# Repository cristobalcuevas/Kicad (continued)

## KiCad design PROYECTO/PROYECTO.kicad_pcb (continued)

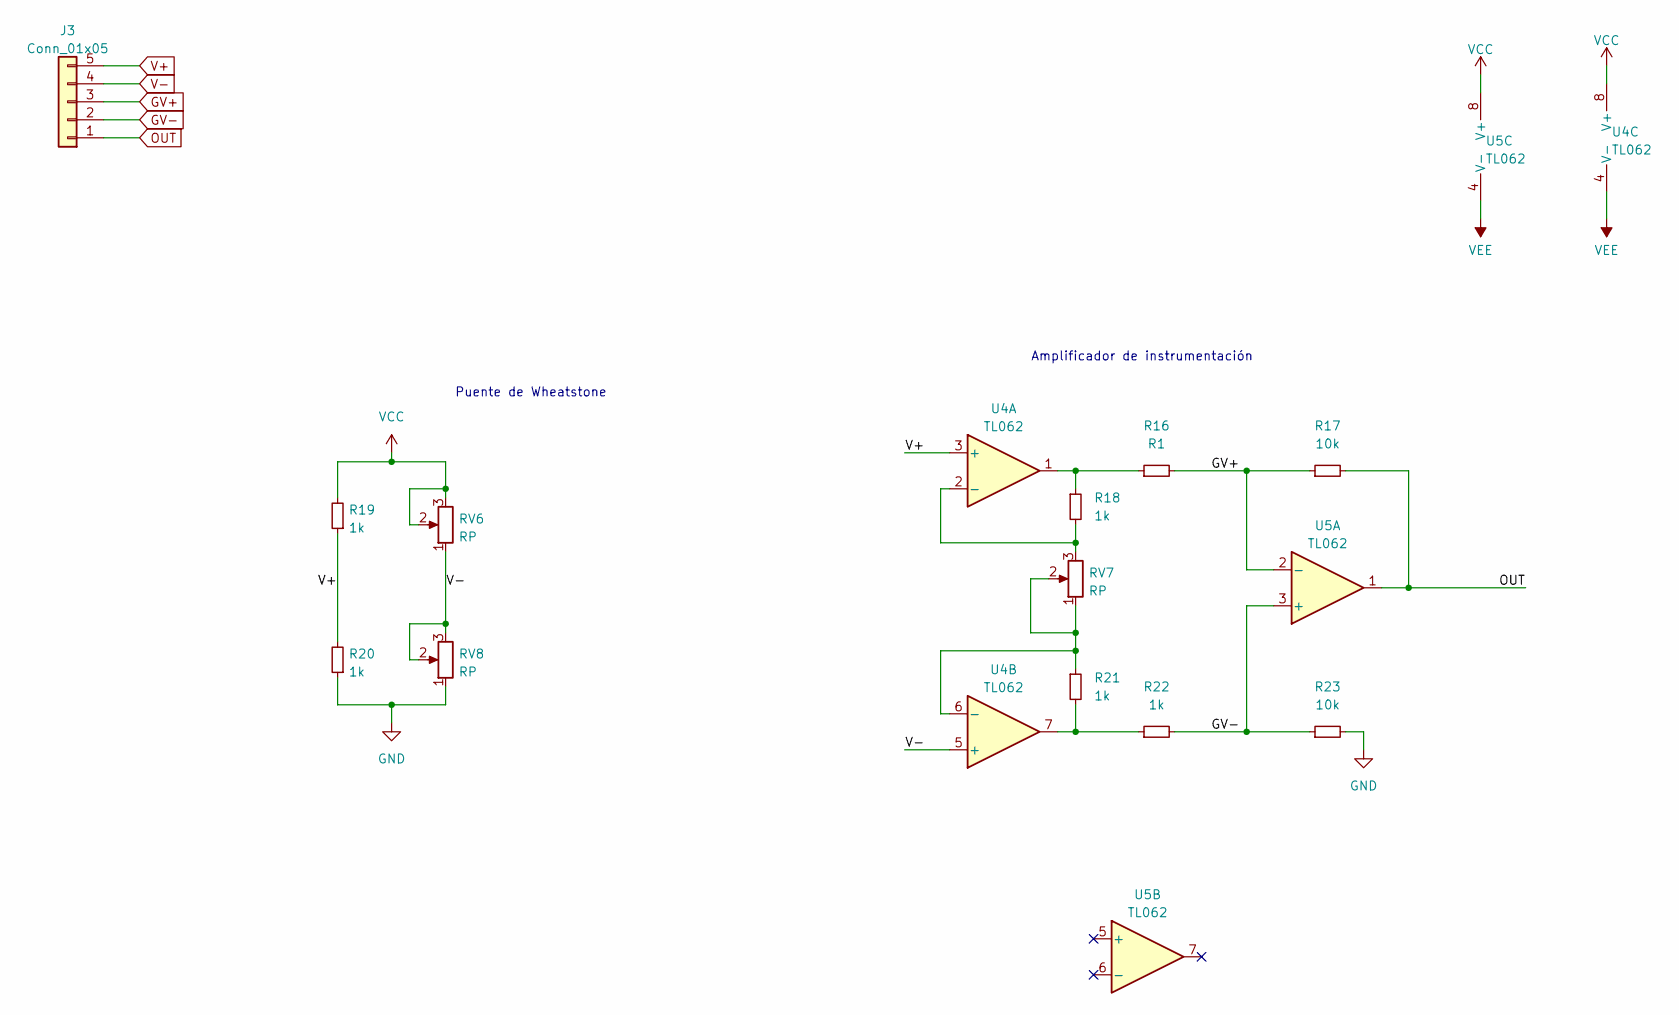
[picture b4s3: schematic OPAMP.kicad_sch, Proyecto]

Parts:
J3: Conn_01x05; PinHeader_1x05_P2.54mm_Vertical
R16: R1; R_Axial_DIN0207_L6.3mm_D2.5mm_P7.62mm_Horizontal
R17, R23: 10k; R_Axial_DIN0207_L6.3mm_D2.5mm_P7.62mm_Horizontal
R18, R19, R20, R21, R22: 1k; R_Axial_DIN0207_L6.3mm_D2.5mm_P7.62mm_Horizontal
RV6, RV7, RV8: RP; PinHeader_1x03_P2.54mm_Vertical
U4, U5: TL062; DIP-8_W7.62mm

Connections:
GND: R20.1, R23.2, RV8.1; also elsewhere on the board
GV+: J3.3, R16.2, R17.1, U5.2 (-)
GV-: J3.2, R22.2, R23.1, U5.3 (+)
unnamed: R16.1, R18.1, U4.1
unnamed: R18.2, RV7.3, U4.2 (-)
unnamed: R21.1, RV7.1, RV7.2, U4.6 (-)
unnamed: R21.2, R22.1, U4.7
OUT: J3.1, R17.2, U5.1
V+: J3.5, R19.1, R20.2, U4.3 (+)
V-: J3.4, RV6.1, RV8.2, RV8.3, U4.5 (+)
VCC: R19.2, RV6.2, RV6.3, U4.8 (V+), U5.8 (V+); also elsewhere on the board
VEE: U4.4 (V-), U5.4 (V-); also elsewhere on the board

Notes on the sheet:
Puente de Wheatstone
Amplificador de instrumentación

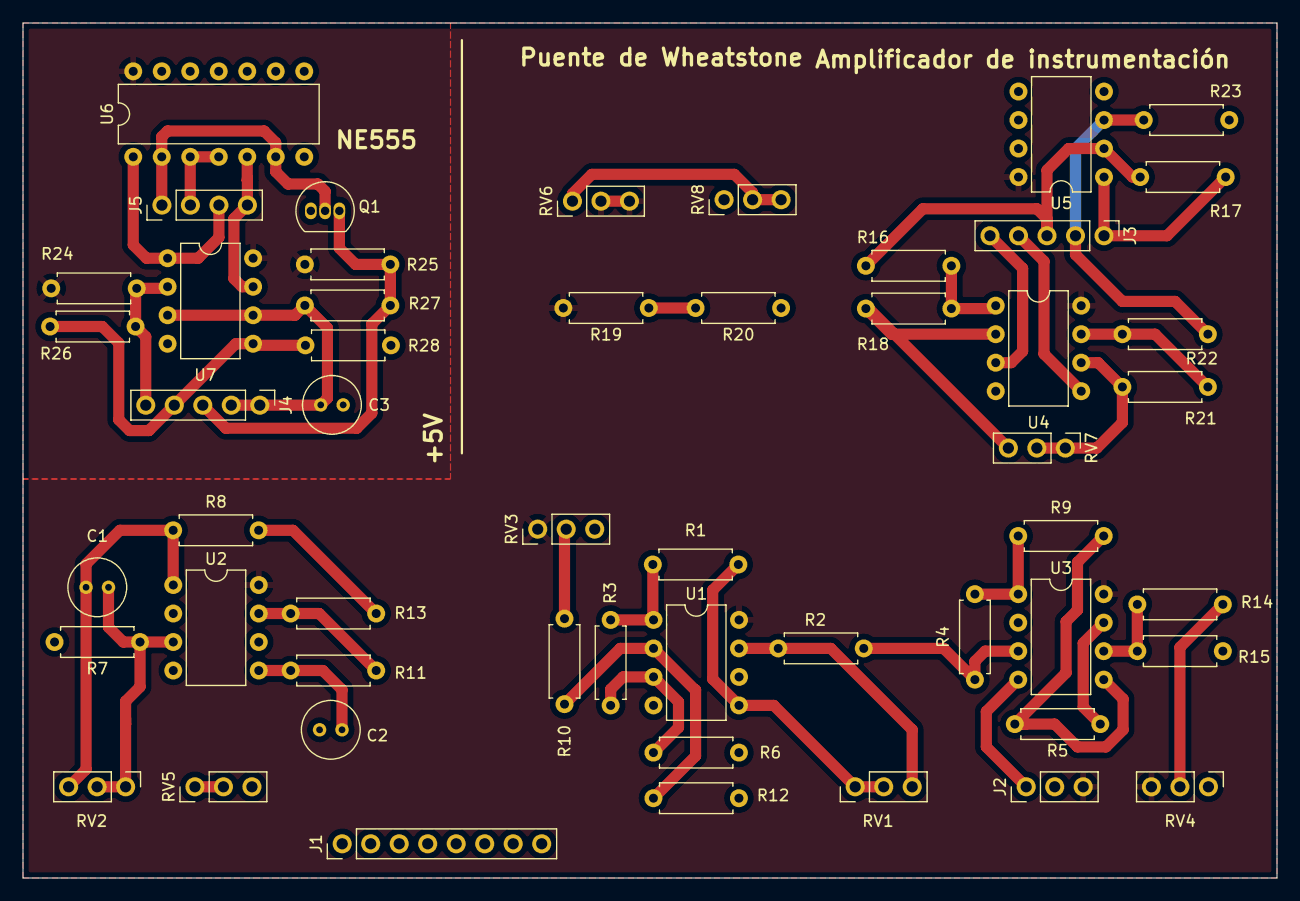
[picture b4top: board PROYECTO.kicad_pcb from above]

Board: 2 copper layers, 111.8 x 76.2 mm, 52 parts (0 on the bottom side), 38 nets.

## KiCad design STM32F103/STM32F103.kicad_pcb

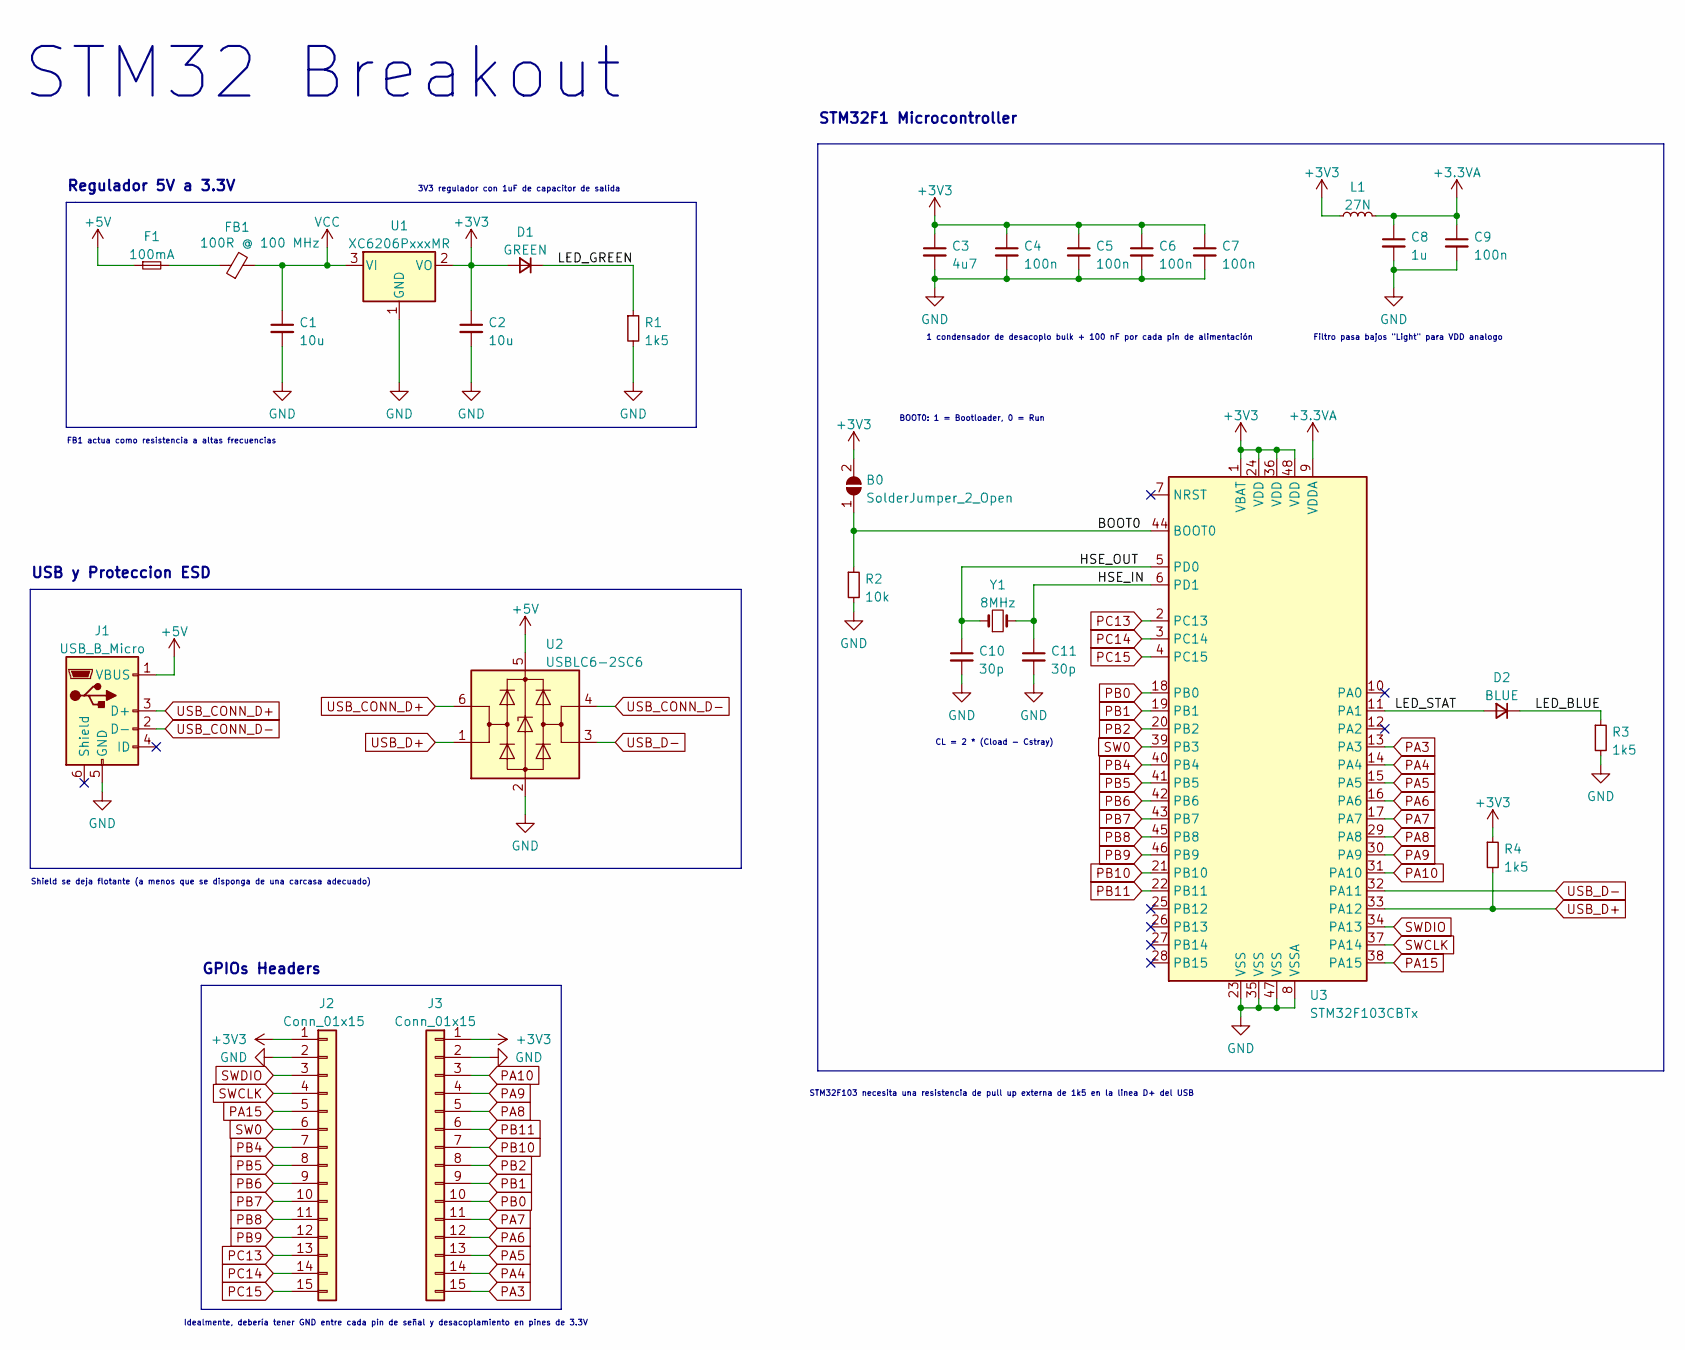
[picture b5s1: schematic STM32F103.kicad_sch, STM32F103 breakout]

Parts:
B0: SolderJumper_2_Open; SolderJumper-2_P1.3mm_Open_Pad1.0x1.5mm
C1, C2: 10u; C_0603_1608Metric
C3: 4u7; C_0603_1608Metric
C4, C5, C6, C7, C9: 100n; C_0402_1005Metric
C8: 1u; C_0402_1005Metric
C10, C11: 30p; C_0402_1005Metric
D1: GREEN; LED_0603_1608Metric
D2: BLUE; LED_0603_1608Metric
F1: 100mA; Fuse_0603_1608Metric
FB1: 100R @ 100 MHz; L_0805_2012Metric
J1: USB_B_Micro; USB_Micro-B_Wuerth_629105150521
J2, J3: Conn_01x15; PinHeader_1x15_P2.54mm_Vertical
L1: 27N; L_0402_1005Metric
R1, R3: 1k5; R_0603_1608Metric
R2: 10k; R_0402_1005Metric
R4: 1k5; R_0402_1005Metric
U1: XC6206PxxxMR; SOT-23
U2: USBLC6-2SC6; SOT-23-6
U3: STM32F103CBTx; LQFP-48_7x7mm_P0.5mm
Y1: 8MHz; Crystal_SMD_5032-2Pin_5.0x3.2mm

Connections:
+3.3VA: C8.1, C9.1, L1.2, U3.9 (VDDA)
+3V3: B0.2 (B), C2.1, C3.1, C4.1, C5.1, C6.1, C7.1, D1.2 (A), J2.1, J3.1, L1.1, R4.1, U1.2 (VO), U3.1 (VBAT), U3.24 (VDD), U3.36 (VDD), U3.48 (VDD)
+5V: F1.1, J1.1 (VBUS), U2.5 (VBUS)
/BOOT0: B0.1 (A), R2.1, U3.44 (BOOT0)
/HSE_IN: C11.1, U3.6 (PD1), Y1.2
/HSE_OUT: C10.1, U3.5 (PD0), Y1.1
/LED_BLUE: D2.1 (K), R3.1
/LED_GREEN: D1.1 (K), R1.1
/LED_STAT: D2.2 (A), U3.11 (PA1)
GND: C1.2, C2.2, C3.2, C4.2, C5.2, C6.2, C7.2, C8.2, C9.2, C10.2, C11.2, J1.5 (GND), J2.2, J3.2, R1.2, R2.2, R3.2, U1.1 (GND), U2.2 (GND), U3.8 (VSSA), U3.23 (VSS), U3.35 (VSS), U3.47 (VSS)
unnamed: F1.2, FB1.1
PA3: J3.15, U3.13 (PA3)
PA4: J3.14, U3.14 (PA4)
PA5: J3.13, U3.15 (PA5)
PA6: J3.12, U3.16 (PA6)
PA7: J3.11, U3.17 (PA7)
PA8: J3.5, U3.29 (PA8)
PA9: J3.4, U3.30 (PA9)
PA10: J3.3, U3.31 (PA10)
PA15: J2.5, U3.38 (PA15)
PB0: J3.10, U3.18 (PB0)
PB1: J3.9, U3.19 (PB1)
PB2: J3.8, U3.20 (PB2)
PB4: J2.7, U3.40 (PB4)
PB5: J2.8, U3.41 (PB5)
PB6: J2.9, U3.42 (PB6)
PB7: J2.10, U3.43 (PB7)
PB8: J2.11, U3.45 (PB8)
PB9: J2.12, U3.46 (PB9)
PB10: J3.7, U3.21 (PB10)
PB11: J3.6, U3.22 (PB11)
PC13: J2.13, U3.2 (PC13)
PC14: J2.14, U3.3 (PC14)
PC15: J2.15, U3.4 (PC15)
SW0: J2.6, U3.39 (PB3)
SWCLK: J2.4, U3.37 (PA14)
SWDIO: J2.3, U3.34 (PA13)
USB_CONN_D+: J1.3 (D+), U2.6 (I/O1)
USB_CONN_D-: J1.2 (D-), U2.4 (I/O2)
USB_D+: R4.2, U2.1 (I/O1), U3.33 (PA12)
USB_D-: U2.3 (I/O2), U3.32 (PA11)
VCC: C1.1, FB1.2, U1.3 (VI)

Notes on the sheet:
Regulador 5V a 3.3V
STM32F1 Microcontroller
STM32F103 necesita una resistencia de pull up externa de 1k5 en la linea D+ del USB
Filtro pasa bajos "Light" para VDD analogo
1 condensador de desacoplo bulk + 100 nF por cada pin de alimentación
FB1 actua como resistencia a altas frecuencias
CL = 2 * (Cload - Cstray)
Idealmente, debería tener GND entre cada pin de señal y desacoplamiento en pines de 3.3V
USB y Proteccion ESD
Shield se deja flotante (a menos que se disponga de una carcasa adecuado)
BOOT0: 1 = Bootloader, 0 = Run
STM32 Breakout
3V3 regulador con 1uF de capacitor de salida
GPIOs Headers

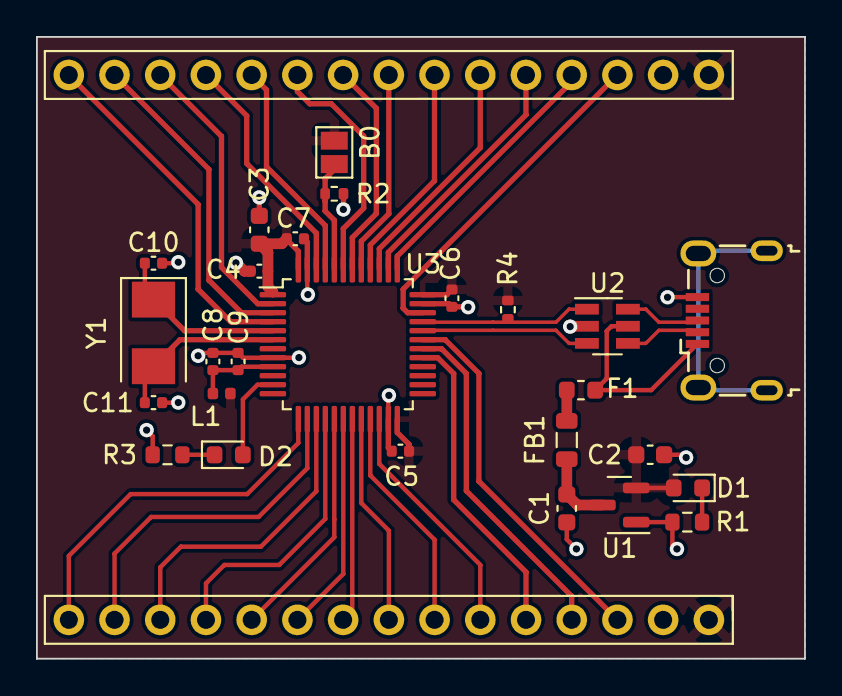
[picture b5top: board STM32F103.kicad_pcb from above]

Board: 2 copper layers, 42.7 x 34.5 mm, 28 parts (0 on the bottom side), 42 nets.

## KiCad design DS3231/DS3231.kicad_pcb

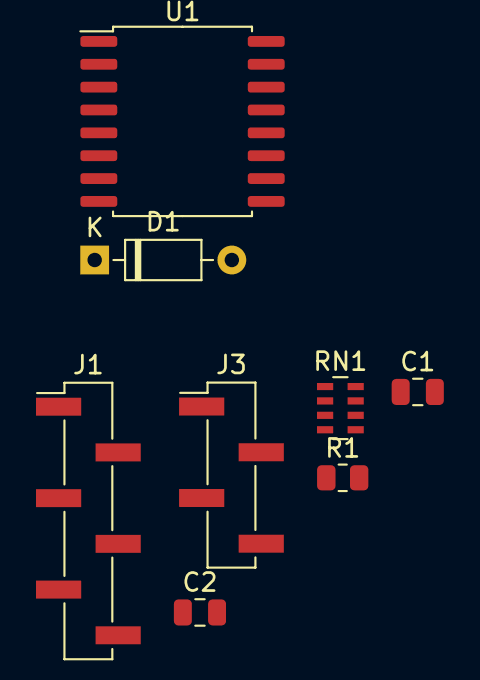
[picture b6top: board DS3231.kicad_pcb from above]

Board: 2 copper layers, 8 parts (0 on the bottom side), 8 nets, no tracks yet.

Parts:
C1: 0.1u; C_0805_2012Metric
C2: 1u; C_0805_2012Metric
D1: 1N4148; D_DO-35_SOD27_P7.62mm_Horizontal
J1: Conn_01x06; PinHeader_1x06_P2.54mm_Vertical_SMD_Pin1Left
J3: Conn_01x04; PinHeader_1x04_P2.54mm_Vertical_SMD_Pin1Left
R1: 200R; R_0805_2012Metric
RN1: 4k7; R_Array_Concave_4x0603
U1: DS3231M; SOIC-16W_7.5x10.3mm_P1.27mm

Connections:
32K: J1.1, RN1.3 (R3.1), U1.1 (32KHZ)
GND: C1.2, C2.2, J1.6, J3.4, U1.5 (GND), U1.6 (GND), U1.7 (GND), U1.8 (GND), U1.9 (GND), U1.10 (GND), U1.11 (GND), U1.12 (GND), U1.13 (GND)
unnamed: D1.2 (A), R1.2
SCL: J1.3, J3.1, RN1.1 (R1.1), U1.16 (SCL)
SDA: J1.4, J3.2, RN1.2 (R2.1), U1.15 (SDA)
SQW: J1.2, RN1.4 (R4.1), U1.3 (~INT/SQW)
VBAT: D1.1 (K), U1.14 (VBAT)
VCC: C1.1, C2.1, J1.5, J3.3, R1.1, RN1.5 (R4.2), RN1.6 (R3.2), RN1.7 (R2.2), RN1.8 (R1.2), U1.2 (VCC)

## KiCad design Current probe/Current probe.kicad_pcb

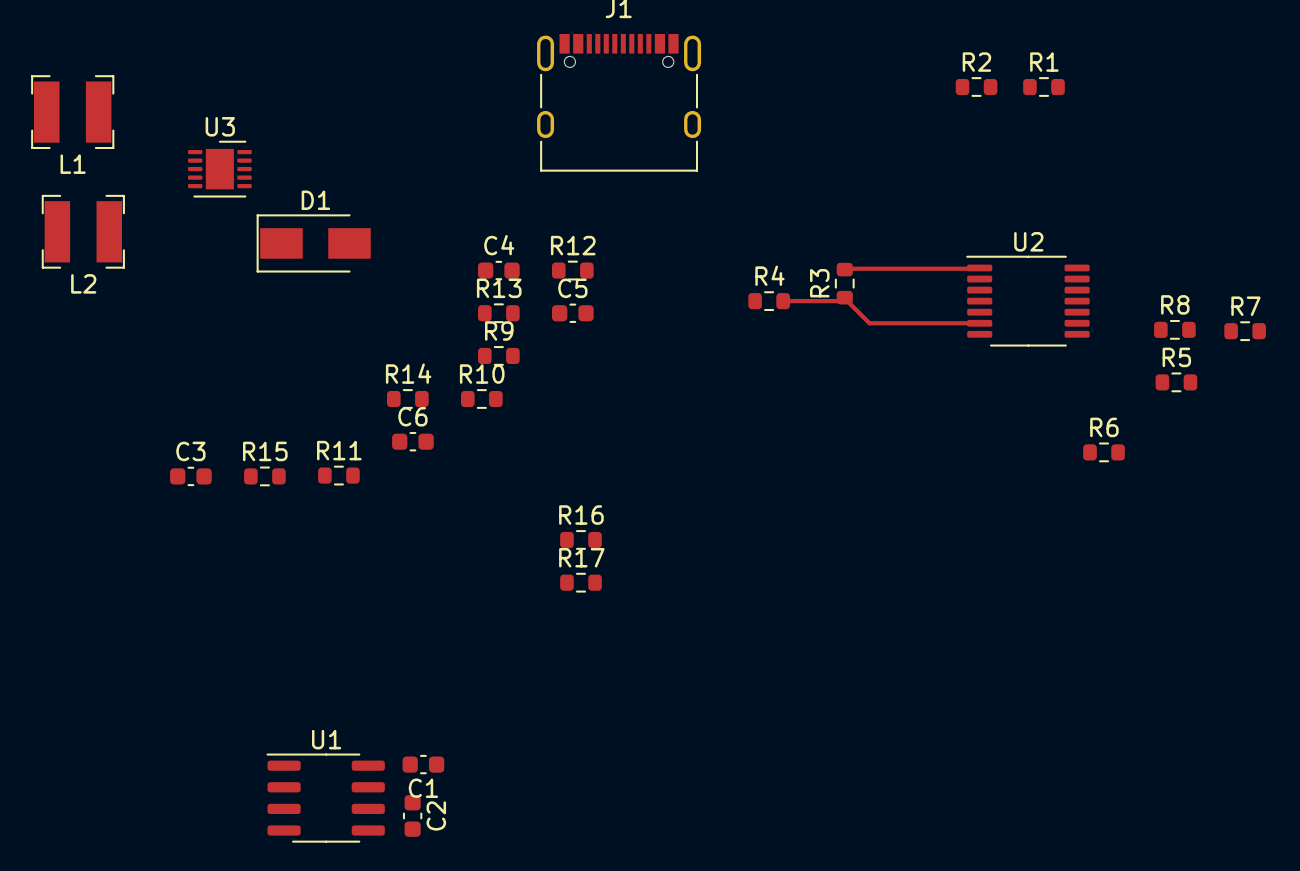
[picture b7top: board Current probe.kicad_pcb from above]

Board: 2 copper layers, 30 parts (0 on the bottom side), 26 nets.

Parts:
C1, C5: 100n; C_0603_1608Metric
C2: 1n; C_0603_1608Metric
C3, C6: 0.47u; C_0603_1608Metric
C4: 1u; C_0603_1608Metric
D1: Schottky; D_SMA
J1: USB_C_Receptacle; USB_C_Receptacle_XKB_U262-16XN-4BVC11
L1, L2: 10u; L_Bourns-SRN4018
R1, R2: 5.1k; R_0603_1608Metric
R3, R4, R5, R6, R7, R8, R9, R10, R11, R17: 10k; R_0603_1608Metric
R12, R13, R14, R15, R16: 1k; R_0603_1608Metric
U1: ACS712xLCTR-05B; SOIC-8_3.9x4.9mm_P1.27mm
U2: ADA4807-4; TSSOP-14_4.4x5mm_P0.65mm
U3: LT3463EDDPBF; DFN-10-1EP_3x3mm_P0.5mm_EP1.65x2.38mm

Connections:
/Amplificador operacional/+5V: C1.2, C4.2, J1.A4 (VBUS), J1.A9 (VBUS), J1.B4 (VBUS), J1.B9 (VBUS), L1.1, L2.1, R3.2, U1.8 (VCC), U3.3 (VIN), U3.8 (~SHDN2), U3.9 (~SHDN1)
/Amplificador operacional/+15V: C3.1, R11.2, U2.4 (V+), U3.1 (VOUT1)
/Amplificador operacional/-15V: C6.1, D1.2 (A), R17.1, U2.11 (V-)
/Amplificador operacional/VOUT: U1.7 (VIOUT), U2.2 (-)
/Fuenta de voltaje/SW2: C5.1, L2.2, U3.4 (SW2)
GND: C1.1, C2.2, C3.2, C4.1, C6.2, J1.A1 (GND), J1.A12 (GND), J1.B1 (GND), J1.B12 (GND), J1.S1 (SHIELD), R1.2, R2.2, R4.1, R6.2, R10.1, R13.1, U1.5 (GND), U3.11 (EPAD)
unnamed: C2.1, U1.6 (FILTER)
unnamed: C5.2, D1.1 (K), U3.5 (D2)
unnamed: J1.A5 (CC1), R2.1
unnamed: J1.B5 (CC2), R1.1
unnamed: U1.3 (IP-), U1.4 (IP-)
unnamed: U1.1 (IP+), U1.2 (IP+)
unnamed: R7.1, U2.8
unnamed: L1.2, U3.2 (SW1)
unnamed: R5.1, R8.2, U2.5 (+)
unnamed: R5.2, U2.12 (+), U2.14
unnamed: R6.1, R7.2, U2.10 (+)
unnamed: R8.1, U2.7, U2.9 (-)
unnamed: R9.2, U2.1, U2.3 (+)
unnamed: R9.1, R10.2, U2.6 (-)
unnamed: R11.1, R12.2
unnamed: R12.1, R13.2, U3.10 (FB1)
unnamed: R14.1, R15.2, U3.6 (FB2)
unnamed: R14.2, U3.7 (VREF)
unnamed: R15.1, R16.2
unnamed: R16.1, R17.2

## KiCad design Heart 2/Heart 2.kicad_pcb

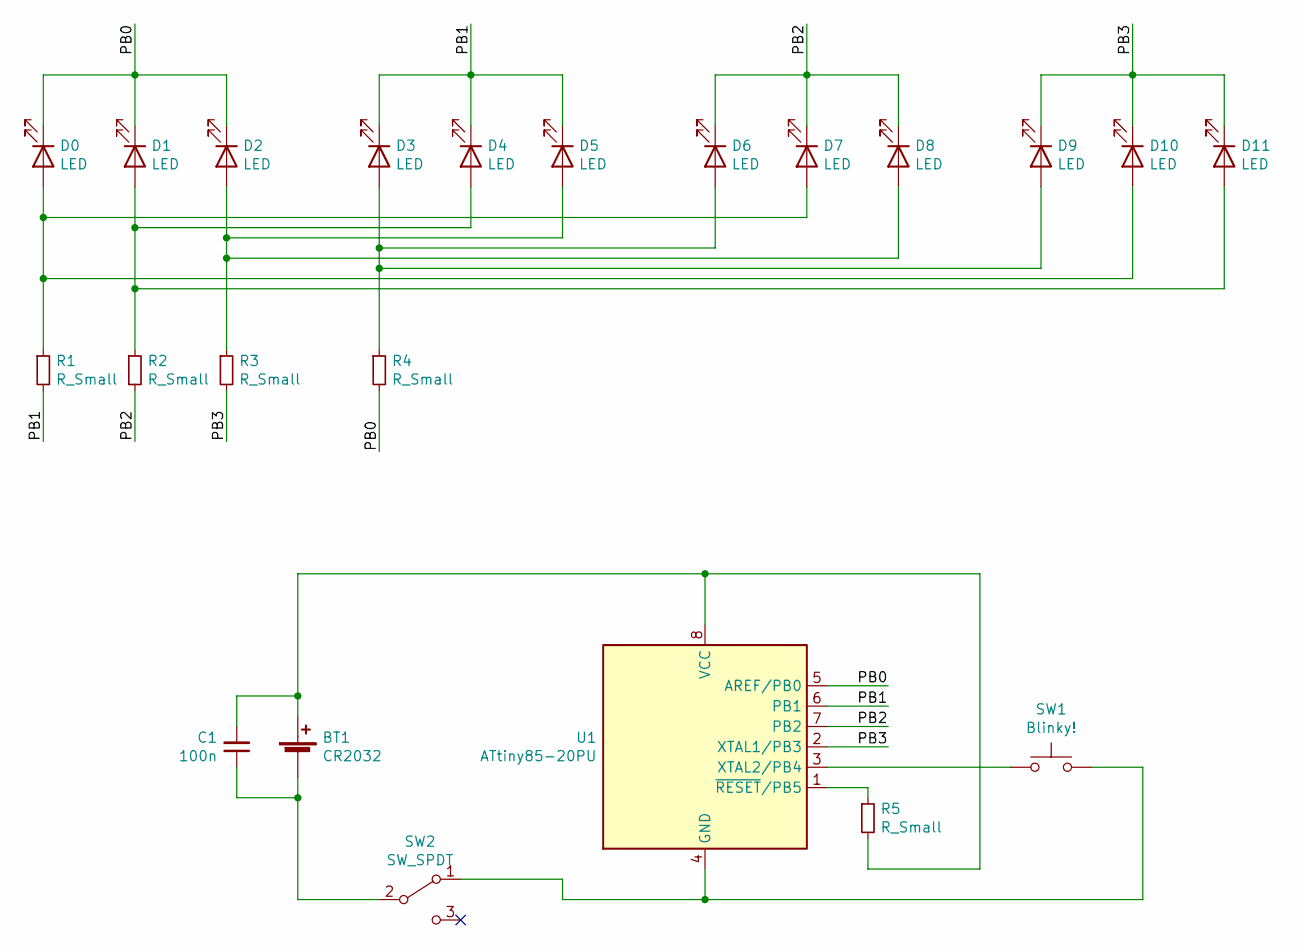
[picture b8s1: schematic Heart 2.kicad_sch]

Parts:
BT1: CR2032; Batteriehalter_CR2032
C1: 100n; C_0805_2012Metric
D0, D1, D2, D3, D4, D5, D6, D7, D8, D9, D10, D11: LED; LED_D5.0mm
R1, R2, R3, R4, R5: R_Small; R_0805_2012Metric
SW1: Blinky!; Taster_SMD_eBay4,5x3mm
SW2: SW_SPDT; 3Pin_Sensor_SMD
U1: ATtiny85-20PU; DIP-8_W7.62mm_Socket

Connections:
/PB0: D0.1 (K), D1.1 (K), D2.1 (K), R4.2, U1.5 (AREF/PB0)
/PB1: D3.1 (K), D4.1 (K), D5.1 (K), R1.2, U1.6 (PB1)
/PB2: D6.1 (K), D7.1 (K), D8.1 (K), R2.2, U1.7 (PB2)
/PB3: D9.1 (K), D10.1 (K), D11.1 (K), R3.2, U1.2 (XTAL1/PB3)
unnamed: BT1.1 (+), C1.2, R5.2, U1.8 (VCC)
unnamed: BT1.2 (-), C1.1, SW2.2 (B)
unnamed: D0.2 (A), D7.2 (A), D10.2 (A), R1.1
unnamed: D1.2 (A), D4.2 (A), D11.2 (A), R2.1
unnamed: D2.2 (A), D5.2 (A), D8.2 (A), R3.1
unnamed: D3.2 (A), D6.2 (A), D9.2 (A), R4.1
unnamed: R5.1, U1.1 (~RESET/PB5)
unnamed: SW1.1, U1.3 (XTAL2/PB4)
unnamed: SW1.2, SW2.1 (A), U1.4 (GND)

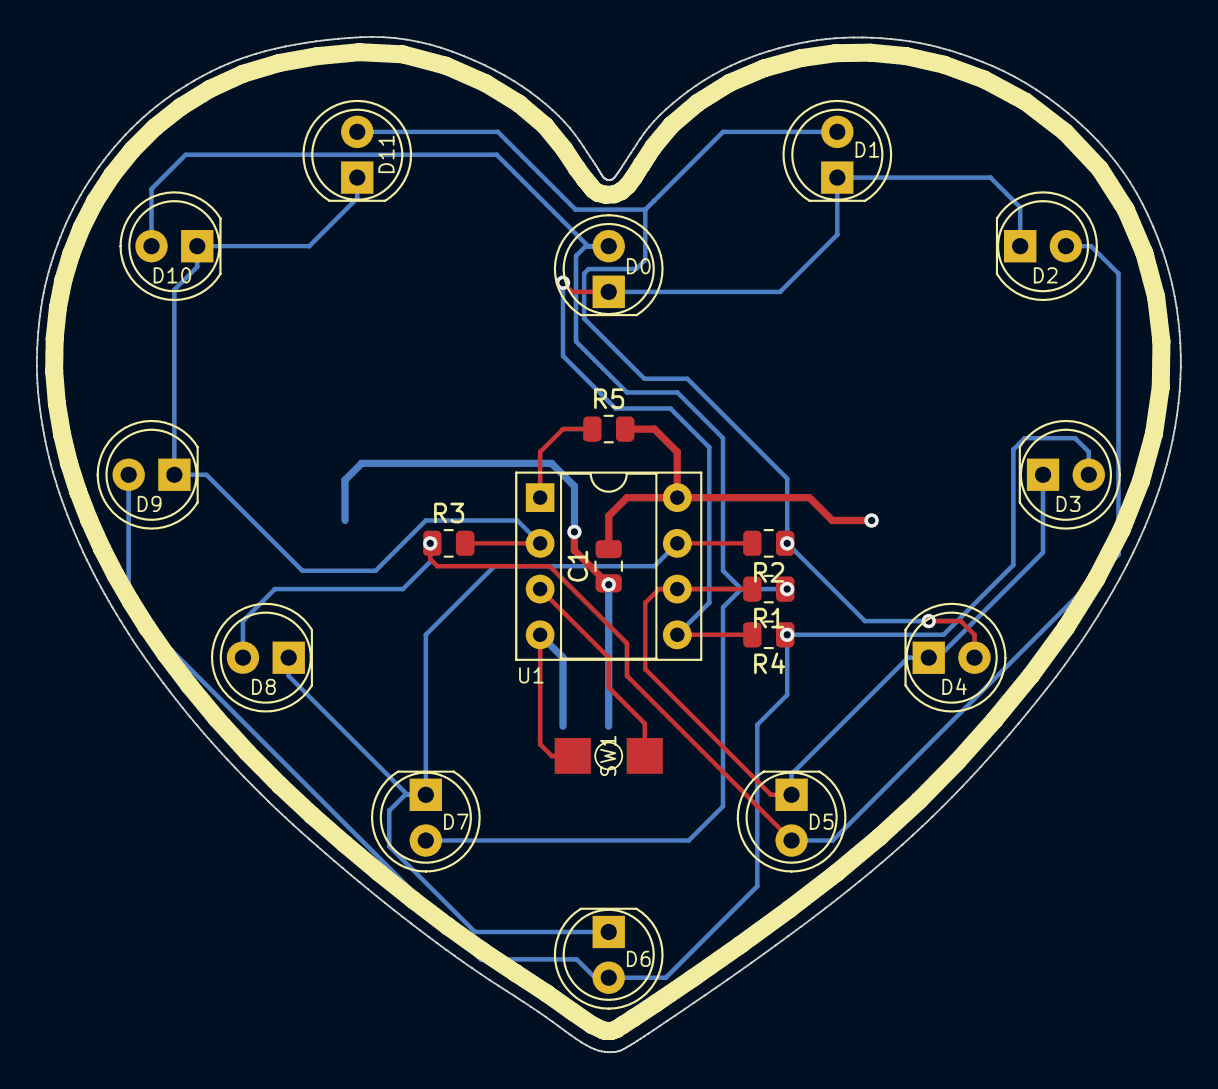
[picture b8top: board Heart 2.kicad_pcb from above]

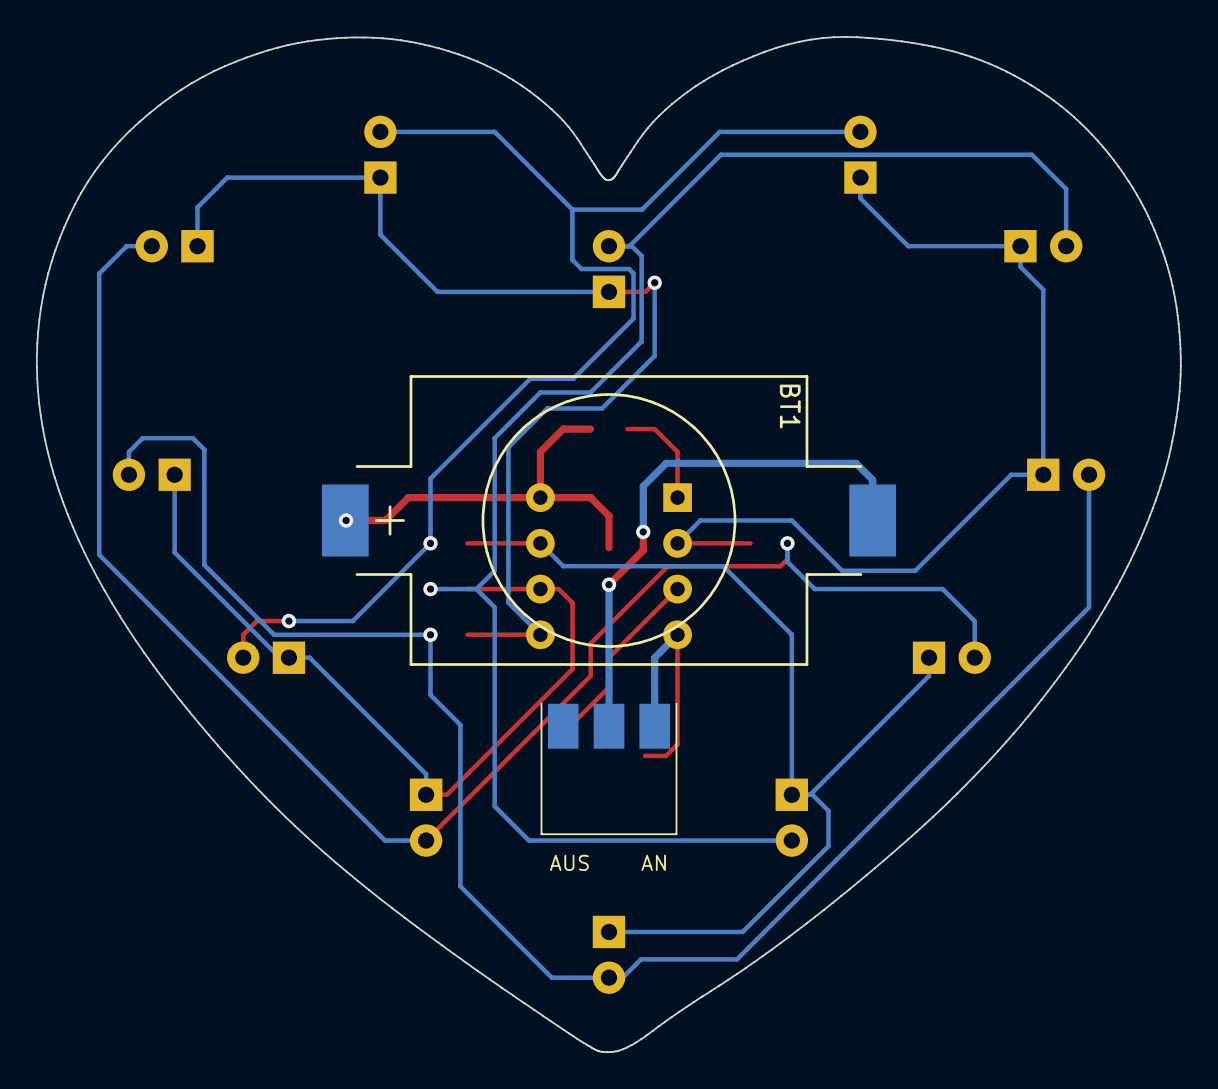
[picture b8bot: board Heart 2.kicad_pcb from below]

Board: 2 copper layers, 63.6 x 56.4 mm, 22 parts (2 on the bottom side), 13 nets.

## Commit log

2022-08-31 project with kicad
2022-09-21 update folders and files
2022-09-25 update files
2022-10-06 update projects
2022-11-06 update schematics
2022-11-06 update mixed signal
